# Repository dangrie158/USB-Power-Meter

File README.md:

# USB Power Meter

<br /><span xmlns:dct="http://purl.org/dc/terms/" property="dct:title">USB Power Meter</span> by <a xmlns:cc="http://creativecommons.org/ns#" href="http://www.nupo-artworks.de" property="cc:attributionName" rel="cc:attributionURL">Daniel Grießhaber</a> is licensed under a <a rel="license" href="http://creativecommons.org/licenses/by-sa/4.0/">Creative Commons Attribution-ShareAlike 4.0 International License</a>.<br />Based on a work at <a xmlns:dct="http://purl.org/dc/terms/" href="https://github.com/dangrie158/USB-Power-Meter" rel="dct:source">https://github.com/dangrie158/USB-Power-Meter</a>.

Since USB has become more and more a power delivery standard, it would be nice to have a convenient way to measure the power consumption these devices need. Of course there are already power meters out there, but they are just boring or don't have all the features I like.

There are two Versions of the board:
One uses a 7 Segment Display module, the other uses a 0.96” OLED Display. The OLED Version is part of the [Hackaday Square Inch Contest](https://hackaday.io/list/7909-square-inch-project-entrants)

## Links

[The Project on Hackaday](https://hackaday.io/project/8197-usb-power-meter)

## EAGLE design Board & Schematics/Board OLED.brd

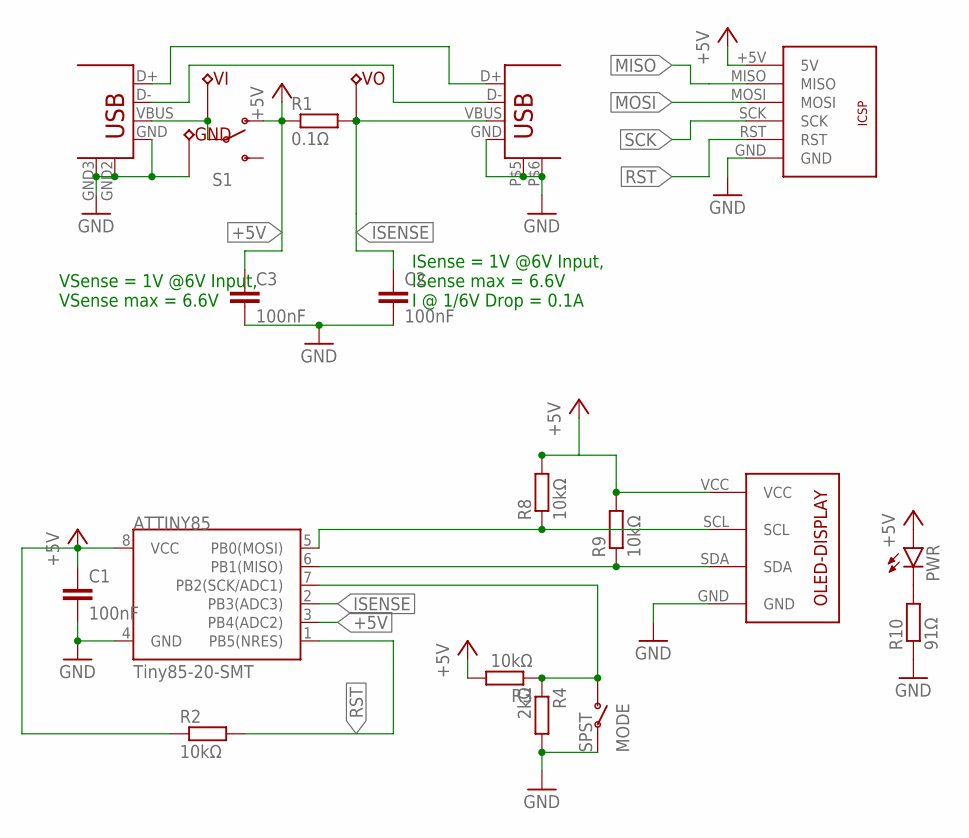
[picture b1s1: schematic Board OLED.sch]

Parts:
ATTINY85: Tiny85-20-SMT; SO08-EIAJ
C1, C2, C3: 100nF; C0603
GND: TESTPOINT0.5MM-DRILL-WIRE-LOOP; TP-0.5MM-DUAL
INPUT: USB+SHIELDTHROUGHHOLE-MALE; USB-A-H
MODE: SPST; WUERTH-SPST-SMD
OUTPUT: USB+SHIELDTHROUGHOLE-FEMALE; USB-A-S-SILK-THROUGHHOLE
PWR: LED0603; LED-0603
R1: 0.1Ω; R2512
R2, R3, R8, R9: 10kΩ; R0603
R4: 2kΩ; R0603
R10: 91Ω; R0603
S1: SWITCH-SPDT-SMD-A; SWITCH-SPST-SMD-A
U$1: ICSPSMD; ICSP-SMD
U$2: OLED-I2C
VI: TESTPOINT0.5MM-DRILL-WIRE-LOOP; TP-0.5MM-DUAL
VO: TESTPOINT0.5MM-DRILL-WIRE-LOOP; TP-0.5MM-DUAL

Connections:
+5V: ATTINY85.3 (PB4(ADC2)), ATTINY85.8 (VCC), C1.1, C3.1, PWR.A, R1.1, R2.1, R3.2, R8.2, R9.2, S1.1 (O), U$1.+5V (5V), U$2.VCC
GND: ATTINY85.4 (GND), C1.2, C2.2, C3.2, GND.P$1, GND.P$2, INPUT.GND, INPUT.GND2 (S1), INPUT.GND3 (S2), MODE.1, MODE.3, OUTPUT.GND, OUTPUT.P$5 (S1), OUTPUT.P$6 (S2), R4.2, R10.1, U$1.GND, U$2.GND
ISENSE: ATTINY85.2 (PB3(ADC3)), C2.1, OUTPUT.VBUS, R1.2, VO.P$1, VO.P$2
MISO: ATTINY85.6 (PB1(MISO)), R9.1, U$1.MISO, U$2.SDA
MOSI: ATTINY85.5 (PB0(MOSI)), R8.1, U$1.MOSI, U$2.SCL
unnamed: INPUT.D+, OUTPUT.D+
unnamed: INPUT.D-, OUTPUT.D-
unnamed: INPUT.VBUS, S1.2, VI.P$1, VI.P$2
unnamed: PWR.C, R10.2
RST: ATTINY85.1 (PB5(NRES)), R2.2, U$1.RST
SCK: ATTINY85.7 (PB2(SCK/ADC1)), MODE.2 (O), MODE.4 (O), R3.1, R4.1, U$1.SCK

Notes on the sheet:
VSense = 1V @6V Input, VSense max = 6.6V
ISense = 1V @6V Input, ISense max = 6.6V I @ 1/6V Drop = 0.1A

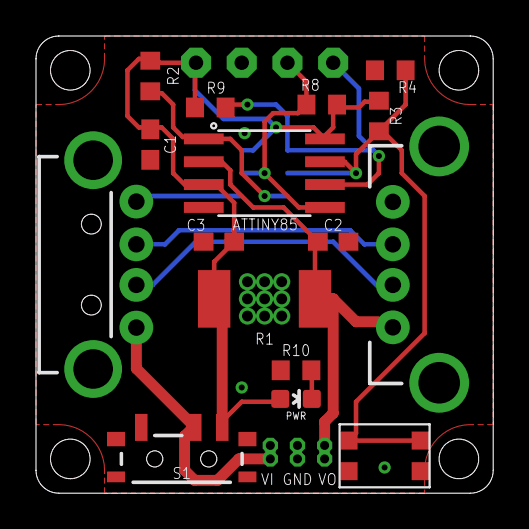
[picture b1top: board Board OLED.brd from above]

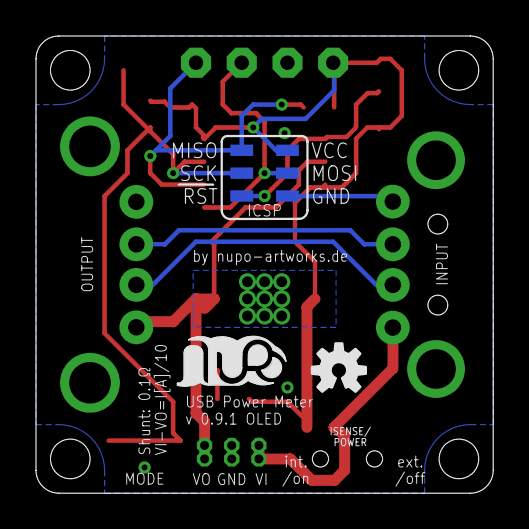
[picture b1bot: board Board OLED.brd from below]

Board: 2 copper layers, 25.4 x 25.4 mm, 23 parts (3 on the bottom side), 11 nets.

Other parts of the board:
U$3: LOGO-SILKSCREEEN-S
U$4: OSHW-LOGO-S

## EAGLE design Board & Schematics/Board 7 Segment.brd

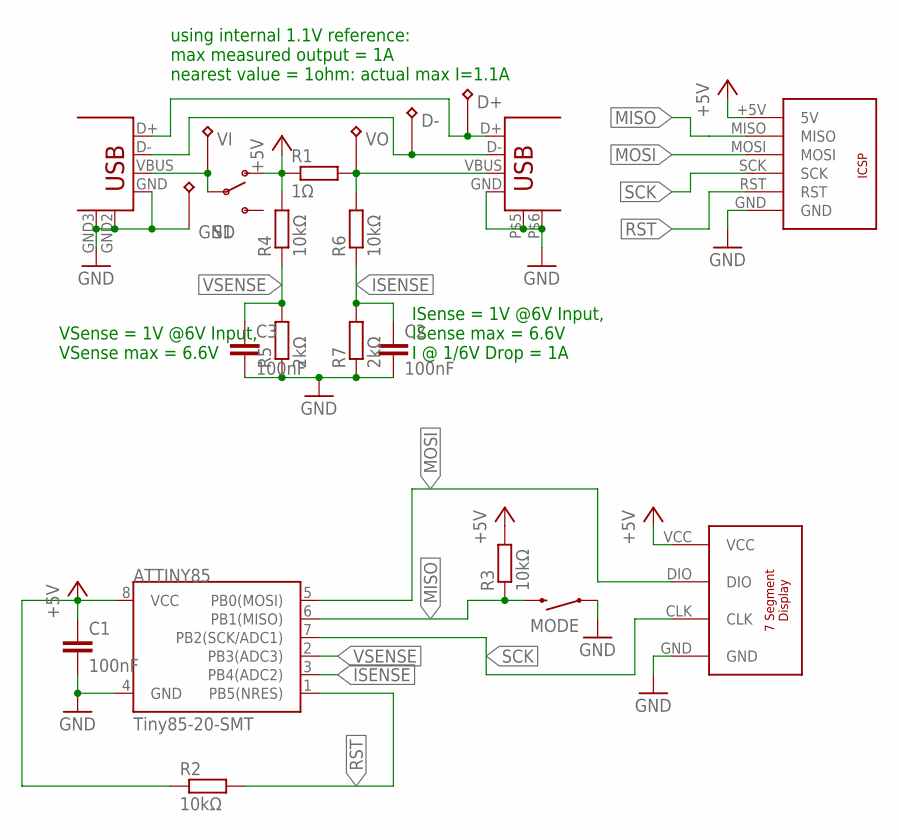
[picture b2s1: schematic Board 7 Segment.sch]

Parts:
ATTINY85: Tiny85-20-SMT; SO08-EIAJ
C1, C2, C3: 100nF; C0603
D+: TESTPOINT0.8MM-DUAL-DRILL-WIRE-LOOP; TP-0.8MM-DUAL
D-: TESTPOINT0.8MM-DUAL-DRILL-WIRE-LOOP; TP-0.8MM-DUAL
GND: TESTPOINT0.8MM-DUAL-DRILL-WIRE-LOOP; TP-0.8MM-DUAL
INPUT: USB+SHIELDTHROUGHHOLE-MALE; USB-A-H
MODE: SWITCH-MOMENTARY-2SIDE_EZ; TACTILE-PTH-SIDEEZ
OUTPUT: USB+SHIELDTHROUGHOLE-FEMALE; USB-A-S-SILK-THROUGHHOLE
R1: 1Ω; R2512
R2, R3, R4, R6: 10kΩ; R0603
R5, R7: 2kΩ; R0603
S1: SWITCH-SPDT-SMD-A; SWITCH-SPST-SMD-A
U$1: ICSPTHROUGHHOLE; ICSP-THROUGHHOLE
U$2: 7-SEGMENT-I2C
VI: TESTPOINT0.8MM-DUAL-DRILL-WIRE-LOOP; TP-0.8MM-DUAL
VO: TESTPOINT0.8MM-DUAL-DRILL-WIRE-LOOP; TP-0.8MM-DUAL

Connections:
+5V: ATTINY85.8 (VCC), C1.1, R1.1, R2.1, R3.2, R4.2, S1.1 (O), U$1.+5V (5V), U$2.VCC
GND: ATTINY85.4 (GND), C1.2, C2.2, C3.2, GND.P$1, GND.P$2, INPUT.GND, INPUT.GND2 (S1), INPUT.GND3 (S2), MODE.1, OUTPUT.GND, OUTPUT.P$5 (S1), OUTPUT.P$6 (S2), R5.1, R7.1, U$1.GND, U$2.GND
ISENSE: ATTINY85.3 (PB4(ADC2)), C2.1, R6.1, R7.2
MISO: ATTINY85.6 (PB1(MISO)), MODE.2, R3.1, U$1.MISO
MOSI: ATTINY85.5 (PB0(MOSI)), U$1.MOSI, U$2.DIO
unnamed: D+.P$1, D+.P$2, INPUT.D+, OUTPUT.D+
unnamed: D-.P$1, D-.P$2, INPUT.D-, OUTPUT.D-
unnamed: INPUT.VBUS, S1.2, VI.P$1, VI.P$2
unnamed: OUTPUT.VBUS, R1.2, R6.2, VO.P$1, VO.P$2
RST: ATTINY85.1 (PB5(NRES)), R2.2, U$1.RST
SCK: ATTINY85.7 (PB2(SCK/ADC1)), U$1.SCK, U$2.CLK
VSENSE: ATTINY85.2 (PB3(ADC3)), C3.1, R4.1, R5.2

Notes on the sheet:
using internal 1.1V reference: max measured output = 1A nearest value = 1ohm: actual max I=1.1A
VSense = 1V @6V Input, VSense max = 6.6V
ISense = 1V @6V Input, ISense max = 6.6V I @ 1/6V Drop = 1A

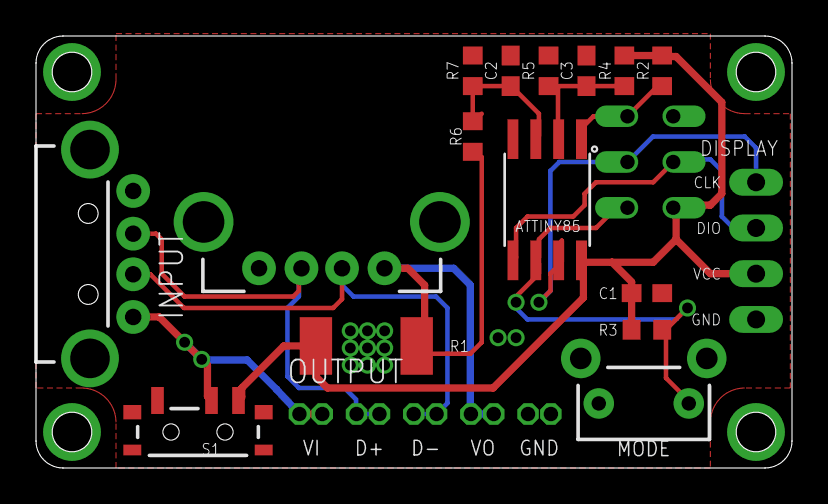
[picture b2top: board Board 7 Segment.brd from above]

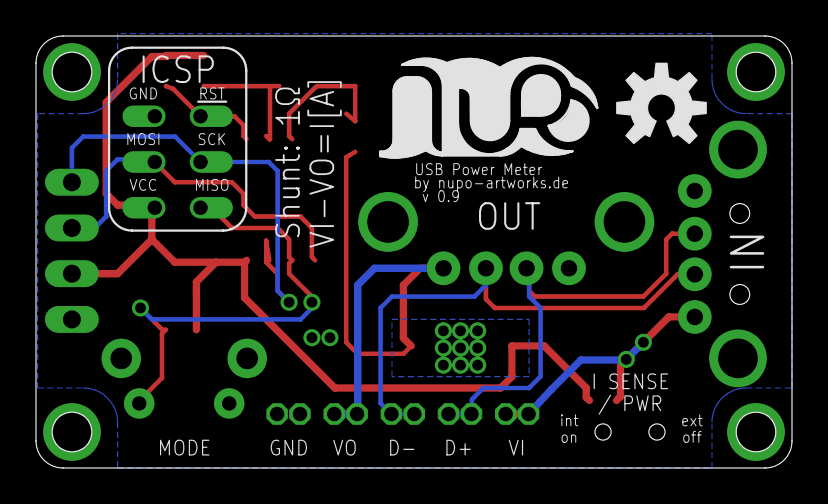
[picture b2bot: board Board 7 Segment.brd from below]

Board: 2 copper layers, 42.0 x 24.0 mm, 24 parts (3 on the bottom side), 12 nets.

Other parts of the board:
U$3: OSHW-LOGO-M
U$5: LOGO-SILKSCREEN

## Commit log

2015-10-25 added schematic and board layout
2015-10-25 added README and .gitignore
2015-10-25 added 3D Model of the assembled board with 7 segment display
2015-10-25 added a Case for 3D Printing
2015-10-25 added new Version of the board that fits on a square inch and uses an OLED display
2015-10-25 switched to markdown README
2015-11-04 removed cream from bottom ICSP Header
2015-11-04 added soldermask from vias
2015-11-04 added soldermask on vias for 7 segment version
2015-11-07 added Licence information
2015-11-11 fixed silkscreen and schematic designator for new, smaller shunt
2015-11-21 remove attenuation from OLED variant
2015-11-23 switched differential measure polarity
2015-11-24 added attenuation resistor network to mode switch pin
2015-12-02 added Gerbers for both versions
2015-12-02 fixed component layout
2015-12-22 added first version of the firmware

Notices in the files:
parts and their libraries:
SparkFun-Connectors: Licensing: Creative Commons ShareAlike 4.0 International - https://creativecommons.org/licenses/by-sa/4.0
